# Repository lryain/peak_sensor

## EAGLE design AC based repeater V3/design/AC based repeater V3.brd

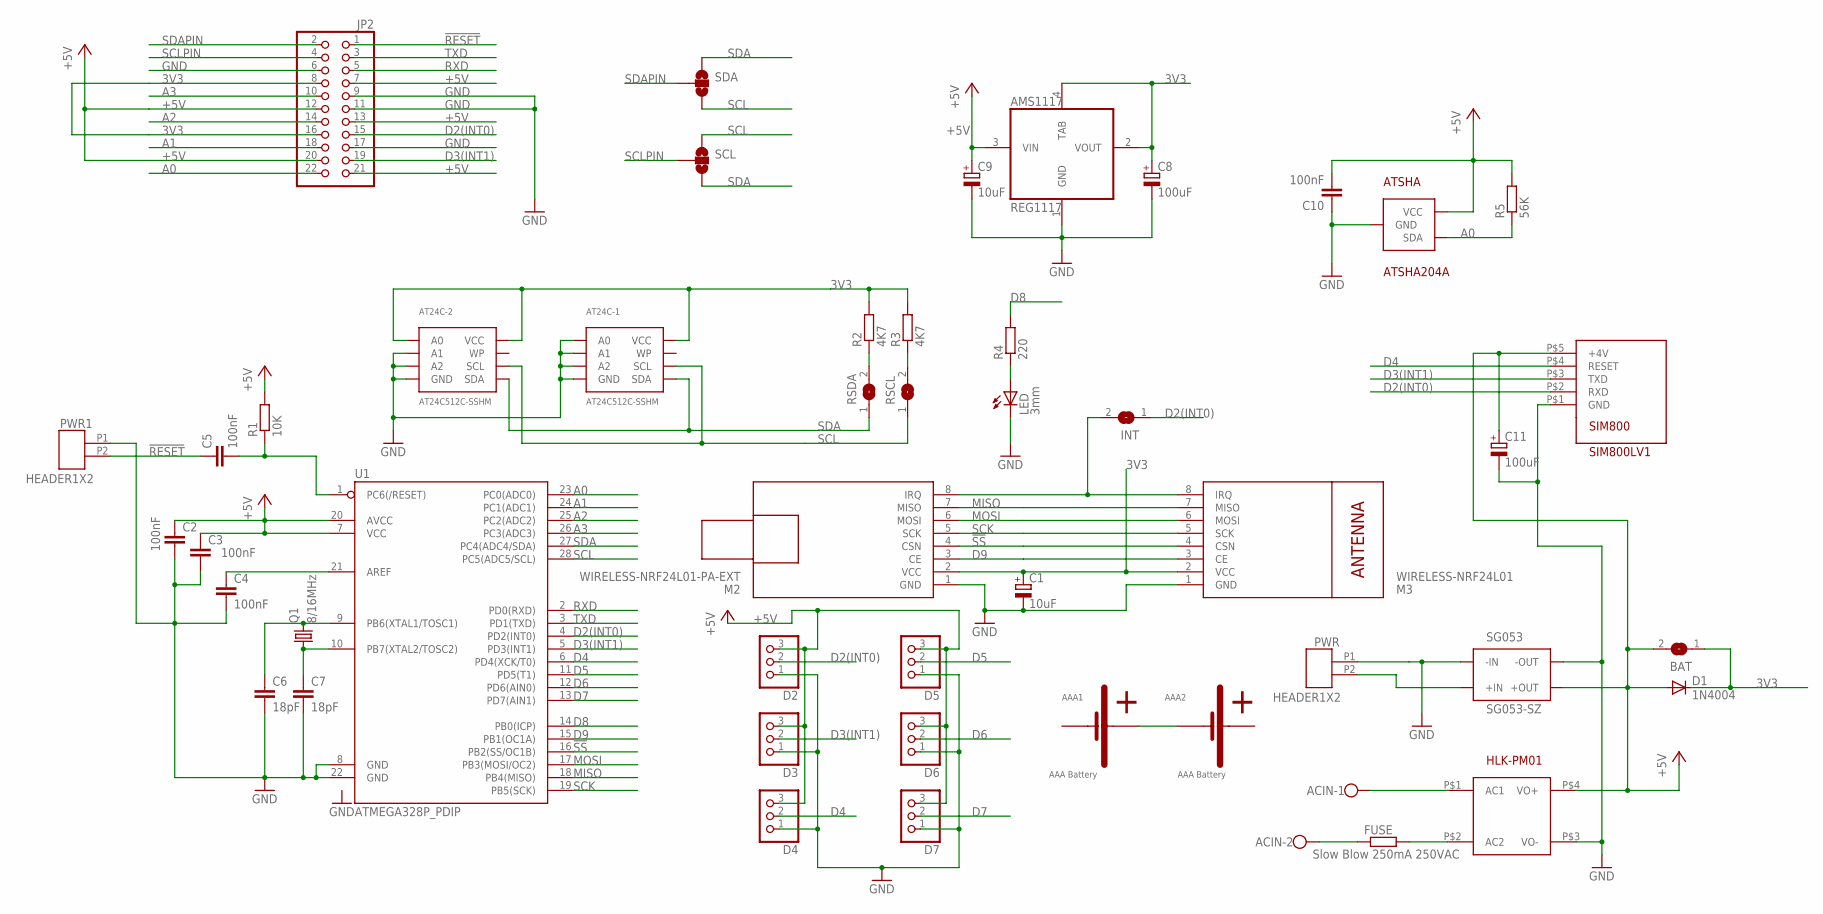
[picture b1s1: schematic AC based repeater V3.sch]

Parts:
AAA1: AAA Battery; AAABATTERYHOLDERPLUSPIN
AAA2: AAA Battery; AAABATTERYHOLDERMINPIN
ACIN: W237-102
AMS1117: REG1117; SOT223
AT24C-1, AT24C-2: AT24C512C-SSHM; SOIC8
ATSHA: ATSHA204A; SOT23-R
BAT: SJ
C1, C9: 10uF; E2,5-5
C2, C3, C4, C5, C10: 100nF; C025-025X050
C6, C7: 18pF; C025-025X050
C8, C11: 100uF; E3,5-8
D1: 1N4004; DO41-10
D2, D3, D4, D5, D6, D7: PINHD-1X3PTH; 1X03
FUSE: Slow Blow 250mA 250VAC; 0411V
HLK-PM01: HLK-PM01
INT: SJ
JP2: PINHD-2X11; 2X11
LED: 3mm; LED3MM
M2: WIRELESS-NRF24L01-PA-EXT; WIRELESS-NRD24L01-PA-EXT
M3: WIRELESS-NRF24L01
PWR, PWR1: HEADER1X2
Q1: 8/16MHz; HC49U-V
R1: 10K; 0207/7
R2, R3: 4K7; 0207/7
R4: 220; 0207/7
R5: 56K; 0207/7
RSCL: SJ
RSDA: SJ
SCL: JUMPER-PAD-3-NC_BY_TRACE; PAD-JUMPER-3-3OF3_NC_BY_TRACE_YES_SILK_FULL_BOX
SDA: JUMPER-PAD-3-NC_BY_TRACE; PAD-JUMPER-3-3OF3_NC_BY_TRACE_YES_SILK_FULL_BOX
SG053: SG053-SZ
SIM800: SIM800LV1
U1: ATMEGA328P_PDIP; DIL28-3

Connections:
3V3: AMS1117.2 (VOUT), AMS1117.4 (TAB), AT24C-1.8 (VCC), AT24C-2.1 (A0), AT24C-2.8 (VCC), BAT.1, C1.+, C8.+, D1.C, JP2.8, JP2.16, M2.2 (VCC), M3.2 (VCC), R2.2, R3.2
!RESET: C5.1, JP2.1, PWR1.P2
!SS: M2.4 (CSN), M3.4 (CSN), U1.16 (PB2(SS/OC1B))
+5V: AMS1117.3 (VIN), ATSHA.2 (VCC), BAT.2, C2.1, C3.1, C9.+, C10.2, C11.+, D1.A, D2.3, D3.3, D4.3, D5.3, D6.3, D7.3, HLK-PM01.P$4 (VO+), JP2.7, JP2.12, JP2.13, JP2.20, JP2.21, R1.2, R5.2, SG053.P$5 (+OUT), SG053.P$6 (+OUT), SIM800.P$5 (+4V), U1.7 (VCC), U1.20 (AVCC)
A0: ATSHA.1 (SDA), JP2.22, R5.1, U1.23 (PC0(ADC0))
A1: JP2.18, U1.24 (PC1(ADC1))
A2: JP2.14, U1.25 (PC2(ADC2))
A3: JP2.10, U1.26 (PC3(ADC3))
D2(INT0): D2.2, INT.1, JP2.15, SIM800.P$2 (RXD), U1.4 (PD2(INT0))
D3(INT1): D3.2, JP2.19, SIM800.P$3 (TXD), U1.5 (PD3(INT1))
D4: D4.2, SIM800.P$4 (RESET), U1.6 (PD4(XCK/T0))
D5: D5.2, U1.11 (PD5(T1))
D6: D6.2, U1.12 (PD6(AIN0))
D7: D7.2, U1.13 (PD7(AIN1))
D8: R4.2, U1.14 (PB0(ICP))
D9: M2.3 (CE), M3.3 (CE), U1.15 (PB1(OC1A))
GND: AMS1117.1 (GND), AT24C-1.1 (A0), AT24C-1.2 (A1), AT24C-1.3 (A2), AT24C-1.4 (GND), AT24C-2.2 (A1), AT24C-2.3 (A2), AT24C-2.4 (GND), ATSHA.3 (GND), C1.-, C2.2, C3.2, C4.2, C6.2, C7.2, C8.-, C9.-, C10.1, C11.-, D2.1, D3.1, D4.1, D5.1, D6.1, D7.1, HLK-PM01.P$3 (VO-), JP2.6, JP2.9, JP2.11, JP2.17, LED.K (C), M2.1 (GND), M3.1 (GND), PWR.P1, PWR1.P1, SG053.P$1 (-IN), SG053.P$2 (-IN), SG053.P$7 (-OUT), SG053.P$8 (-OUT), SIM800.P$1 (GND), U1.8 (GND), U1.22 (GND)
MISO: M2.7 (MISO), M3.7 (MISO), U1.18 (PB4(MISO))
MOSI: M2.6 (MOSI), M3.6 (MOSI), U1.17 (PB3(MOSI/OC2))
unnamed: PWR.P2, SG053.P$3 (+IN), SG053.P$4 (+IN)
unnamed: R2.1, RSDA.2
unnamed: ACIN.2, FUSE.1
unnamed: C4.1, U1.21 (AREF)
unnamed: R3.1, RSCL.2
unnamed: AAA1.P$2, AAA2.P$1
unnamed: ACIN.1, HLK-PM01.P$1 (AC1)
unnamed: FUSE.2, HLK-PM01.P$2 (AC2)
unnamed: C5.2, R1.1, U1.1 (PC6(/RESET))
unnamed: INT.2, M2.8 (IRQ), M3.8 (IRQ)
unnamed: LED.A, R4.1
unnamed: C6.1, Q1.2, U1.9 (PB6(XTAL1/TOSC1))
unnamed: C7.1, Q1.1, U1.10 (PB7(XTAL2/TOSC2))
RXD: JP2.5, U1.2 (PD0(RXD))
SCK: M2.5 (SCK), M3.5 (SCK), U1.19 (PB5(SCK))
SCL: AT24C-1.6 (SCL), AT24C-2.6 (SCL), RSCL.1, SCL.1, SDA.3, U1.28 (PC5(ADC5/SCL))
SCLPIN: JP2.4, SCL.2
SDA: AT24C-1.5 (SDA), AT24C-2.5 (SDA), RSDA.1, SCL.3, SDA.1, U1.27 (PC4(ADC4/SDA))
SDAPIN: JP2.2, SDA.2
TXD: JP2.3, U1.3 (PD1(TXD))

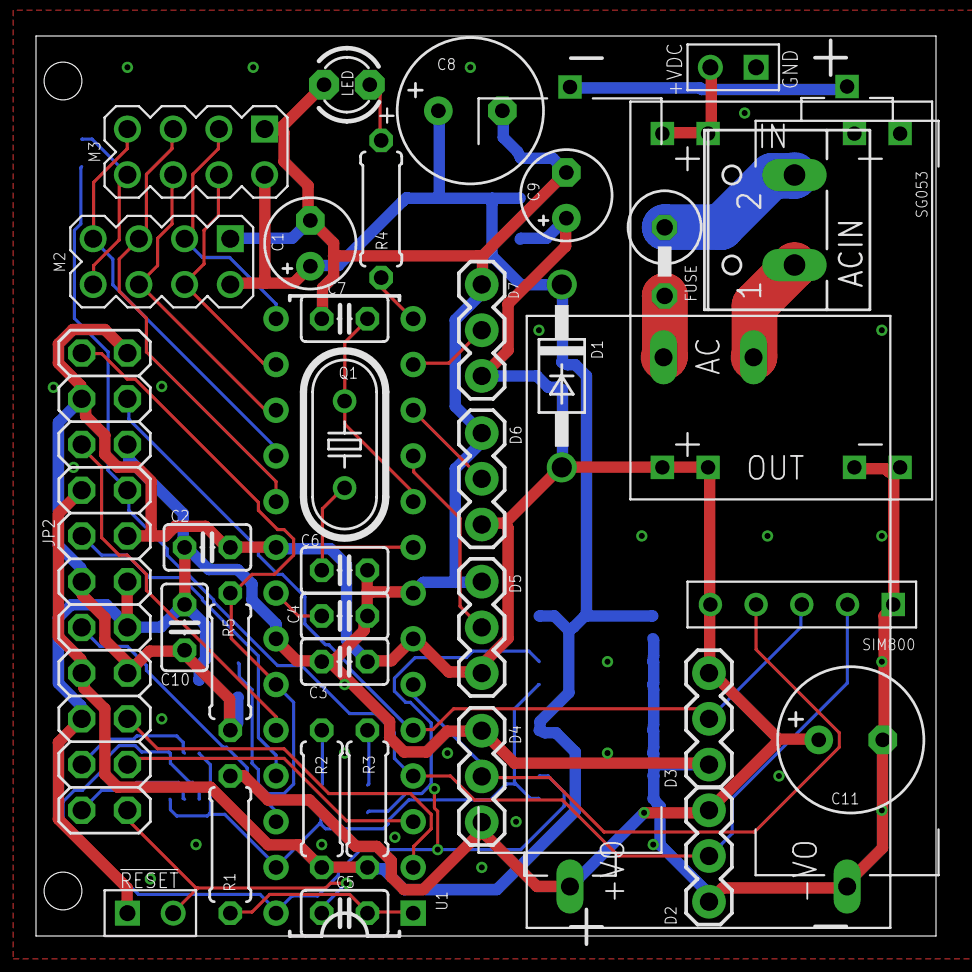
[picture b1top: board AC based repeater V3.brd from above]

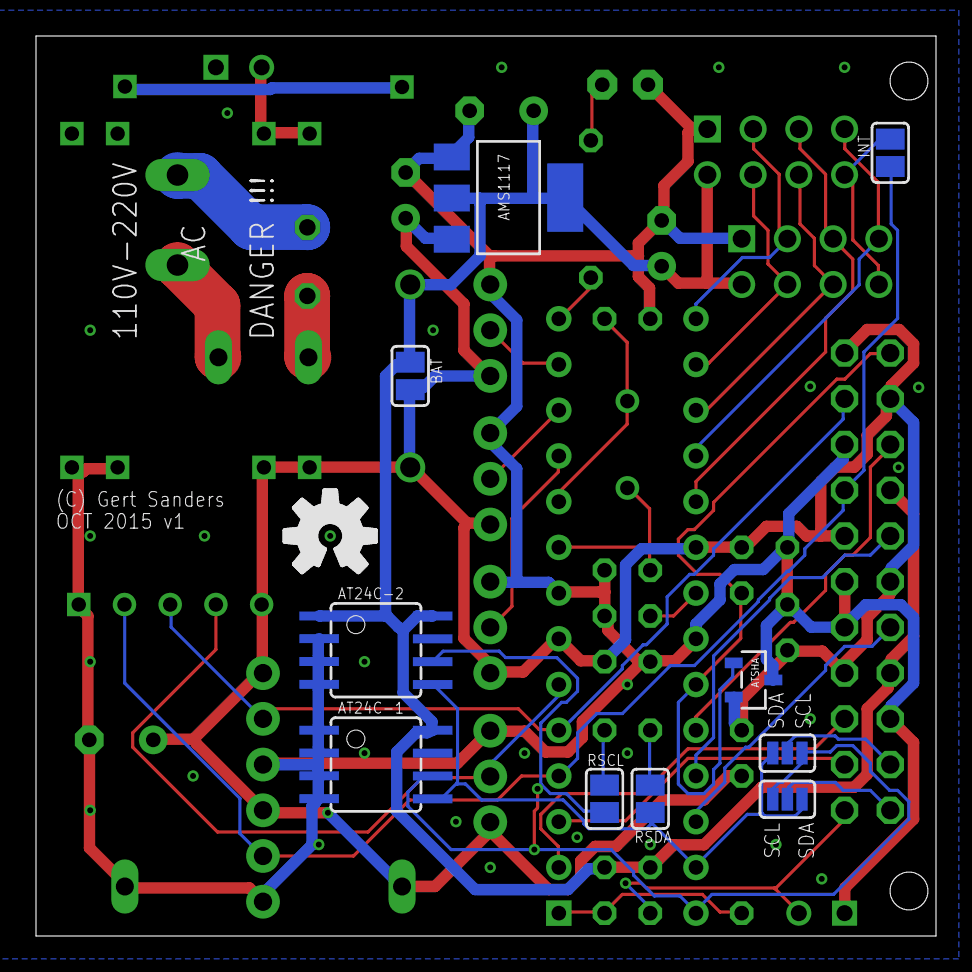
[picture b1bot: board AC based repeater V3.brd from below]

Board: 2 copper layers, 50.0 x 50.0 mm, 49 parts (11 on the bottom side), 39 nets.

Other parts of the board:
U$1: OSHWLOGO_TOL_0.2

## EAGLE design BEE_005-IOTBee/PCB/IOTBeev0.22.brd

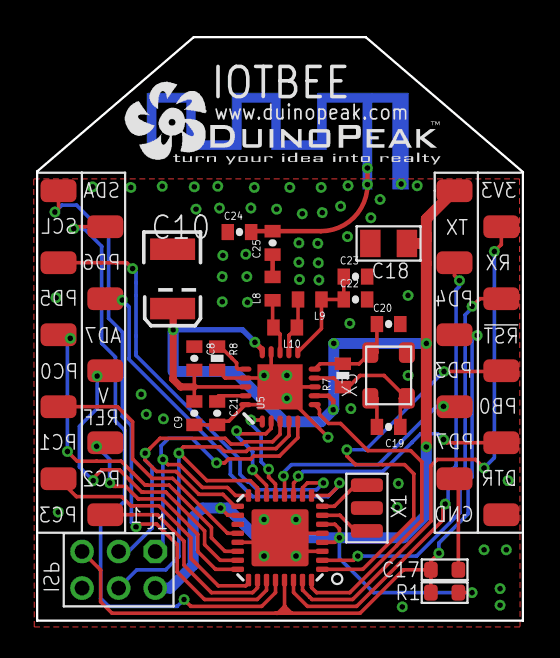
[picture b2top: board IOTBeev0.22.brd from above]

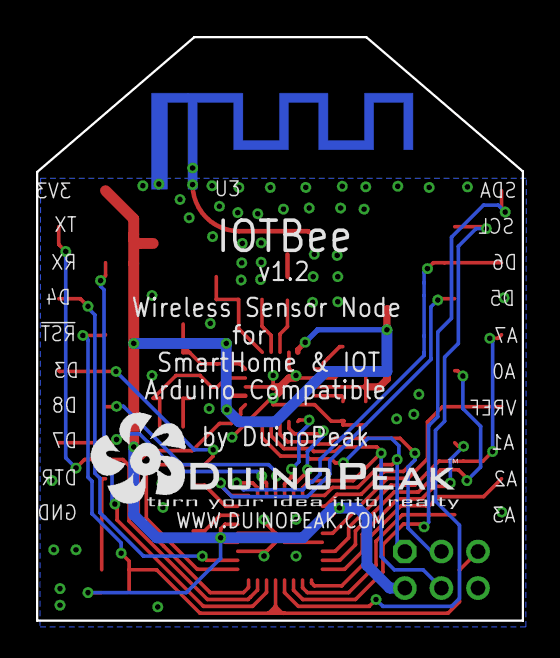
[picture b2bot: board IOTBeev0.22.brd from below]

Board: 2 copper layers, 27.0 x 32.4 mm, 27 parts (3 on the bottom side), 37 nets.

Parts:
ANT1: 2.4G-ANT
C8: 10nF; 0402-CAP
C9: 1nF; 0402-CAP
C10: 10uF; EIA3528
C17: 100nF; 0603_S
C18: 10u; 0805
C19, C20: 22pF; 0402-CAP
C21: 33nF; 0402-CAP
C22: 2.2nF; 0402-CAP
C23: 4.7pF; 0402-CAP
C24: 1.0pF; 0402-CAP
C25: 1.5pF; 0402-CAP
J1: CK_2X3_2.0
L8: 3.9nH; C0402
L9: 2.7nH; C0402
L10: 8.2nH; C0402
R1: 10k; 0603_S
R7: 1M; 0402-RES
R8: 22K; 0402-RES
U1: MEGA8; MLF32X
U3: 20P-SMD-2.0-BT
U5: NRF24L01ALT1; QFN20_ALT1
U$2: DUINOPEAK-LOGO-0.6
U$3: DUINOPEAK-LOGO-0.7
X1: 8MHz; XTAL_3X2
X3: 16MHz; X3225

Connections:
!RESET: C17.2, J1.3, R1.2, U1.29, U3.5
+3V3: C8.2, C9.2, C10.A, C18.1, J1.6, R1.1, U1.4, U1.6, U1.18, U3.1, U5.7, U5.15, U5.18
ADC7: U1.22, U3.16
ANT: ANT1.2, C24.2, C25.2
AREF: U1.20, U3.14
CE: U1.13, U5.1
CSN: U1.14, U5.2
DTR: C17.1, U3.9
GND: ANT1.1, C8.1, C9.1, C10.C, C18.2, C19.2, C20.2, C21.2, C22.2, C23.2, C24.1, J1.4, R8.2, U1.3, U1.5, U1.21, U1.HEAT, U3.10, U5.0, U5.8, U5.14, U5.17, U5.20, X1.2, X3.1, X3.3
IRQ: U1.32, U5.6
MISO: J1.1, U1.16, U5.5
MOSI: J1.5, U1.15, U5.4
unnamed: U1.7, X1.1
unnamed: U1.8, X1.3
unnamed: C19.1, R7.1, U5.9, X3.2
unnamed: C20.1, R7.2, U5.10, X3.4
unnamed: L8.1, L10.2, U5.13
unnamed: C22.1, C23.1, L9.1, U5.11
unnamed: R8.1, U5.16
unnamed: C21.1, U5.19
unnamed: L9.2, L10.1, U5.12
unnamed: C25.1, L8.2
PB0: U1.12, U3.7
PC0: U1.23, U3.15
PC1: U1.24, U3.13
PC2: U1.25, U3.12
PC3: U1.26, U3.11
PD3: U1.1, U3.6
PD4: U1.2, U3.4
PD5: U1.9, U3.17
PD6: U1.10, U3.18
PD7: U1.11, U3.8
RX: U1.30, U3.3
SCK: J1.2, U1.17, U5.3
SCL: U1.28, U3.19
SDA: U1.27, U3.20
TX: U1.31, U3.2

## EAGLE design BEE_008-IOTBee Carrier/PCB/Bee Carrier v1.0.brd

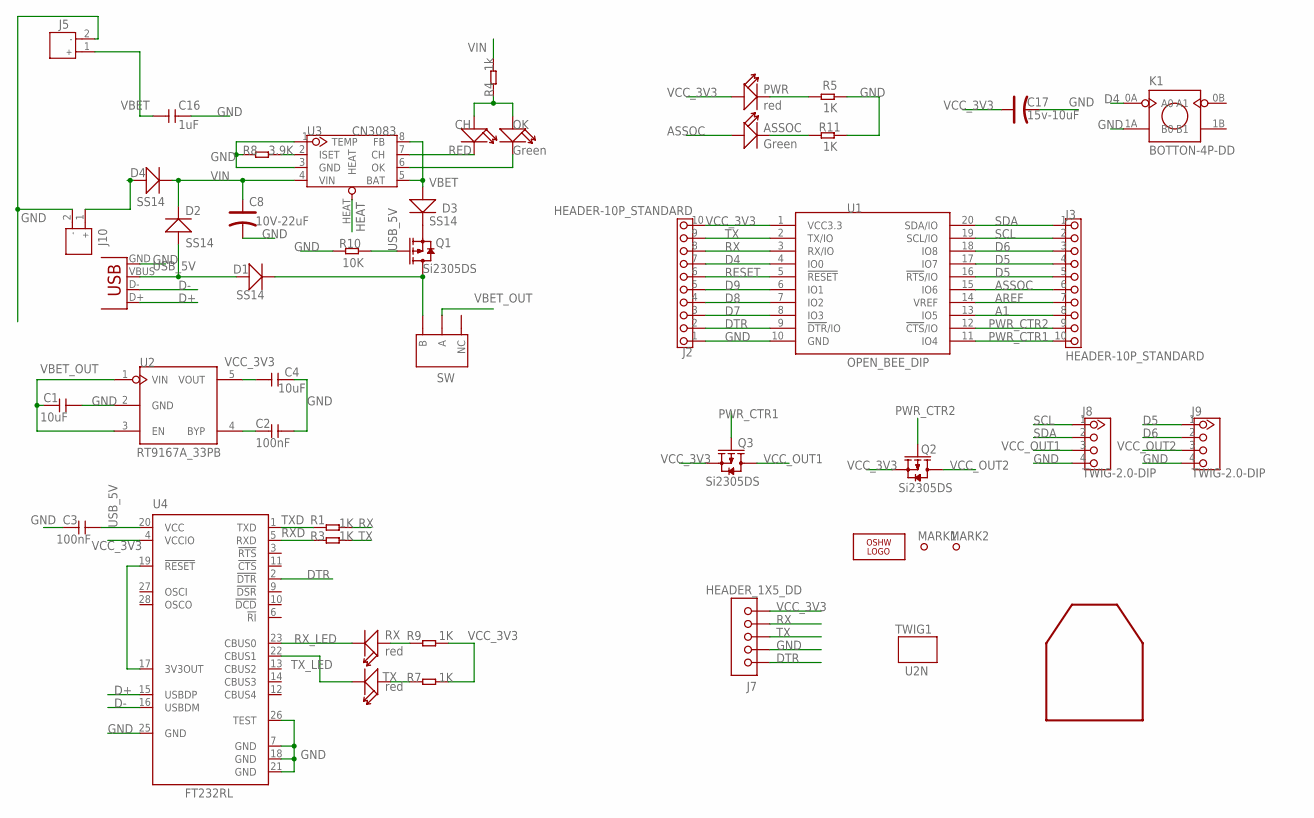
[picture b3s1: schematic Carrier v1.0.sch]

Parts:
ASSOC: Green; D0603
C1, C4: 10uF; 0805
C2, C3: 100nF; 0603
C8: 10V-22uF; AVX-B
C16: 1uF; 0805
C17: 15v-10uF; AVX-A
CH: RED; D0603
D1, D2, D3, D4: SS14; D2010
J2, J3: HEADER-10P_STANDARD; 2.54_10P
J5, J10: JST-2P-POWER-LEADED; 2P-2.0-LEADED-4.7X6.0
J7: HEADER_1X5_DD; CK_1X5
J8, J9: TWIG-2.0-DIP; 2.0_1X4
K1: BOTTON-4P-DD; BTN-S
LOGO2: OSHW_LOGO_FILLX0200-NT; OSHW_FILLX200_NOTEXT
MARK1, MARK2: PAD-MARK; MARK
OK: Green; D0603
PWR: red; D0805
Q1, Q2, Q3: Si2305DS; SOT23
R1, R3, R5, R7, R9, R11: 1K; 0603
R4: 1k; 0603
R8: 3.9K; 0603
R10: 10K; 0603
RX: red; D0603
SW: SWITCH-3P; 008-SW-3P-DIP
TWIG1: U2N; U2N_SILK
TX: red; D0603
U1: OPEN_BEE_DIP; CCBEE-PRO
U2: RT9167A_33PB; SOT23-5
U3: CN3083; SOP8
U4: FT232RL; SSOP28
U$1: WIFI_SILK
X1: USB-SMD-NS; USB-MINIB-NOSTOP

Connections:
A1: J3.8, U1.13 (IO5); also elsewhere on the board
AREF: J3.7, U1.14 (VREF); also elsewhere on the board
ASSOC: ASSOC.+, J3.6, U1.15 (IO6); also elsewhere on the board
D4: J2.7, K1.0A (A0), U1.4 (IO0); also elsewhere on the board
D5: J3.4, J3.5, J9.1, U1.16 (!RTS!/IO), U1.17 (IO7); also elsewhere on the board
D6: J3.3, J9.2, U1.18 (IO8); also elsewhere on the board
D7: J2.3, U1.8 (IO3); also elsewhere on the board
D8: J2.4, U1.7 (IO2); also elsewhere on the board
D9: J2.5, U1.6 (IO1); also elsewhere on the board
D+: U4.15 (USBDP), X1.D+
D-: U4.16 (USBDM), X1.D-
DTR: J2.2, J7.1, U1.9 (!DTR!/IO), U4.2 (!DTR); also elsewhere on the board
GND: C1.2, C2.2, C3.1, C4.2, C8.-, C16.2, C17.-, J2.1, J5.2, J7.2, J8.4, J9.4, J10.2, K1.1A (B0), R5.1, R8.1, R10.1, R11.1, U1.10 (GND), U2.2 (GND), U3.1 (TEMP), U3.3 (GND), U4.7 (GND), U4.18 (GND), U4.21 (GND), U4.25 (GND), U4.26 (TEST), X1.GND; also elsewhere on the board
HEAT: U3.HEAT
unnamed: PWR.-, R5.2
unnamed: R8.2, U3.2 (ISET)
unnamed: D4.+, J10.1
unnamed: C2.1, U2.4 (BYP)
unnamed: CH.-, U3.7 (CH)
unnamed: OK.-, U3.6 (OK)
unnamed: CH.+, OK.+, R4.1
unnamed: U4.17 (3V3OUT), U4.19 (!RESET)
unnamed: D3.-, Q1.2 (S)
unnamed: ASSOC.-, R11.2
unnamed: D1.-, Q1.3 (D), SW.P$3 (B)
unnamed: R9.1, RX.+
unnamed: R7.1, TX.+
PWR_CTR1: J3.10, Q3.1 (G), U1.11 (IO4); also elsewhere on the board
PWR_CTR2: J3.9, Q2.1 (G), U1.12 (!CTS!/IO); also elsewhere on the board
RESET: J2.6, U1.5 (!RESET); also elsewhere on the board
RX: J2.8, J7.4, R1.2, U1.3 (RX/IO); also elsewhere on the board
RXD: R3.1, U4.5 (RXD)
RX_LED: RX.-, U4.23 (CBUS0)
SCL: J3.2, J8.1, U1.19 (SCL/IO); also elsewhere on the board
SDA: J3.1, J8.2, U1.20 (SDA/IO); also elsewhere on the board
TX: J2.9, J7.3, R3.2, U1.2 (TX/IO); also elsewhere on the board
TXD: R1.1, U4.1 (TXD)
TX_LED: TX.-, U4.22 (CBUS1)
USB_5V: C3.2, D1.+, D2.+, Q1.1 (G), R10.2, U4.20 (VCC), X1.VBUS
VBET: C16.1, D3.+, J5.1, U3.5 (BAT), U3.8 (FB)
VBET_OUT: C1.1, SW.P$2 (A), U2.1 (VIN), U2.3 (EN)
VCC_3V3: C4.1, C17.+, J2.10, J7.5, PWR.+, Q2.2 (S), Q3.2 (S), R7.2, R9.2, U1.1 (VCC3.3), U2.5 (VOUT), U4.4 (VCCIO); also elsewhere on the board
VCC_OUT1: J8.3, Q3.3 (D)
VCC_OUT2: J9.3, Q2.3 (D)
VIN: C8.+, D2.-, D4.-, R4.2, U3.4 (VIN)

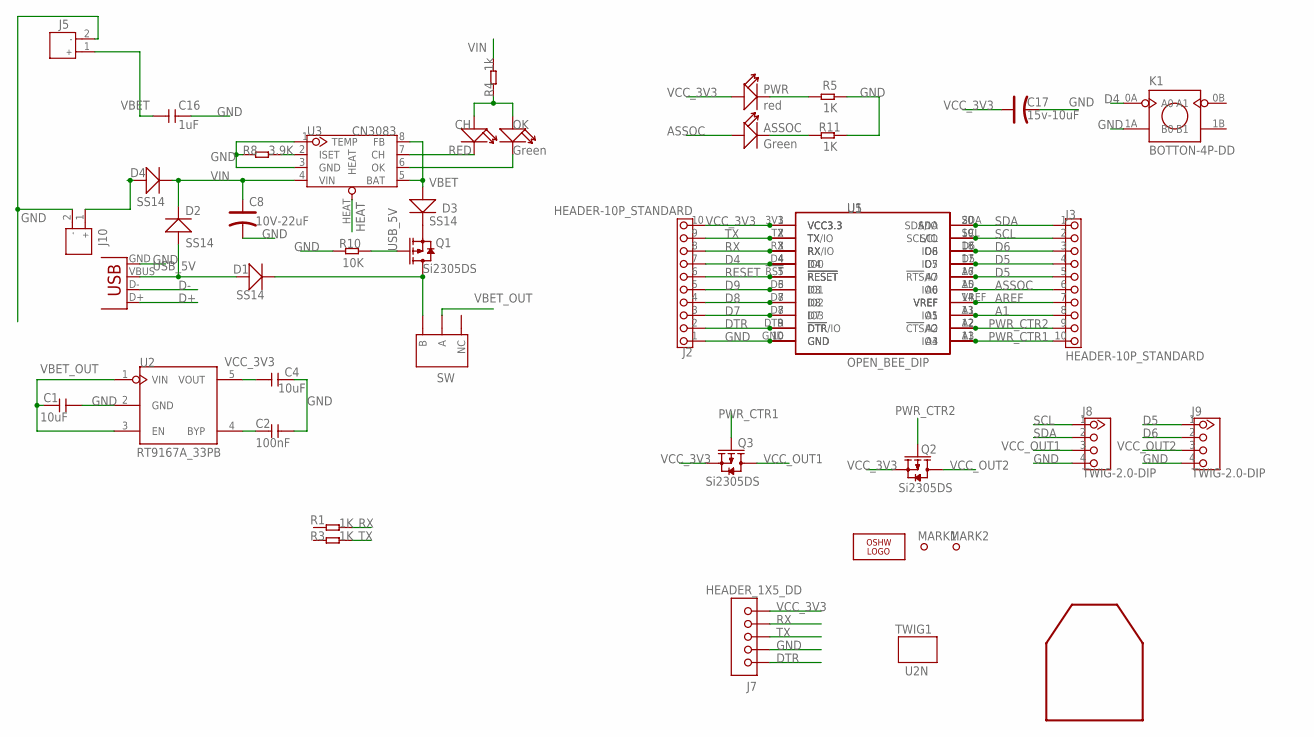
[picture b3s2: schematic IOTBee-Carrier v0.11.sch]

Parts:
ASSOC: Green; D0603
C1, C4: 10uF; 0805
C2: 100nF; 0603
C8: 10V-22uF; AVX-B
C16: 1uF; 0805
C17: 15v-10uF; AVX-A
CH: RED; D0603
D1, D2, D3, D4: SS14; D2010
J2, J3: HEADER-10P_STANDARD; 2.54_10P
J5, J10: JST-2P-POWER-LEADED; 2P-2.0-LEADED-4.7X6.0
J7: HEADER_1X5_DD; CK_1X5
J8, J9: TWIG-2.0-DIP; 2.0_1X4
K1: BOTTON-4P-DD; BTN-S
LOGO2: OSHW_LOGO_FILLX0200-NT; OSHW_FILLX200_NOTEXT
MARK1, MARK2: PAD-MARK; MARK
OK: Green; D0603
PWR: red; D0805
Q1, Q2, Q3: Si2305DS; SOT23
R1, R3, R5, R11: 1K; 0603
R4: 1k; 0603
R8: 3.9K; 0603
R10: 10K; 0603
SW: SWITCH-3P; 008-SW-3P-DIP
TWIG1: U2N; U2N_SILK
U1: OPEN_BEE_DIP; CCBEE-PRO
U2: RT9167A_33PB; SOT23-5
U3: CN3083; SOP8
U5: BEE-IOTBEE-IOTBEE-SOCKET; IOT_BEE_SMD
U$1: WIFI_SILK
X1: USB-SMD-NS; USB-MINIB-NOSTOP

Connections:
A1: J3.8, U1.13 (IO5), U5.A1
AREF: J3.7, U1.14 (VREF), U5.VREF
ASSOC: ASSOC.+, J3.6, U1.15 (IO6), U5.A0
D4: J2.7, K1.0A (A0), U1.4 (IO0), U5.D4
D5: J3.4, J3.5, J9.1, U1.16 (!RTS!/IO), U1.17 (IO7), U5.A7, U5.D5
D6: J3.3, J9.2, U1.18 (IO8), U5.D6
D7: J2.3, U1.8 (IO3), U5.D7
D8: J2.4, U1.7 (IO2), U5.D8
D9: J2.5, U1.6 (IO1), U5.D3
D+: X1.D+; also elsewhere on the board
D-: X1.D-; also elsewhere on the board
DTR: J2.2, J7.1, U1.9 (!DTR!/IO), U5.DTR (!DTR); also elsewhere on the board
GND: C1.2, C2.2, C4.2, C8.-, C16.2, C17.-, J2.1, J5.2, J7.2, J8.4, J9.4, J10.2, K1.1A (B0), R5.1, R8.1, R10.1, R11.1, U1.10 (GND), U2.2 (GND), U3.1 (TEMP), U3.3 (GND), U5.GND, X1.GND; also elsewhere on the board
HEAT: U3.HEAT
unnamed: PWR.-, R5.2
unnamed: R8.2, U3.2 (ISET)
unnamed: D4.+, J10.1
unnamed: C2.1, U2.4 (BYP)
unnamed: CH.-, U3.7 (CH)
unnamed: OK.-, U3.6 (OK)
unnamed: CH.+, OK.+, R4.1
unnamed: D3.-, Q1.2 (S)
unnamed: ASSOC.-, R11.2
unnamed: D1.-, Q1.3 (D), SW.P$3 (B)
PWR_CTR1: J3.10, Q3.1 (G), U1.11 (IO4), U5.A3
PWR_CTR2: J3.9, Q2.1 (G), U1.12 (!CTS!/IO), U5.A2
RESET: J2.6, U1.5 (!RESET), U5.!RST (!RESET)
RX: J2.8, J7.4, R1.2, U1.3 (RX/IO), U5.RX
SCL: J3.2, J8.1, U1.19 (SCL/IO), U5.SCL
SDA: J3.1, J8.2, U1.20 (SDA/IO), U5.SDA
TX: J2.9, J7.3, R3.2, U1.2 (TX/IO), U5.TX
USB_5V: D1.+, D2.+, Q1.1 (G), R10.2, X1.VBUS; also elsewhere on the board
VBET: C16.1, D3.+, J5.1, U3.5 (BAT), U3.8 (FB)
VBET_OUT: C1.1, SW.P$2 (A), U2.1 (VIN), U2.3 (EN)
VCC_3V3: C4.1, C17.+, J2.10, J7.5, PWR.+, Q2.2 (S), Q3.2 (S), U1.1 (VCC3.3), U2.5 (VOUT), U5.3V3 (VCC3.3); also elsewhere on the board
VCC_OUT1: J8.3, Q3.3 (D)
VCC_OUT2: J9.3, Q2.3 (D)
VIN: C8.+, D2.-, D4.-, R4.2, U3.4 (VIN)

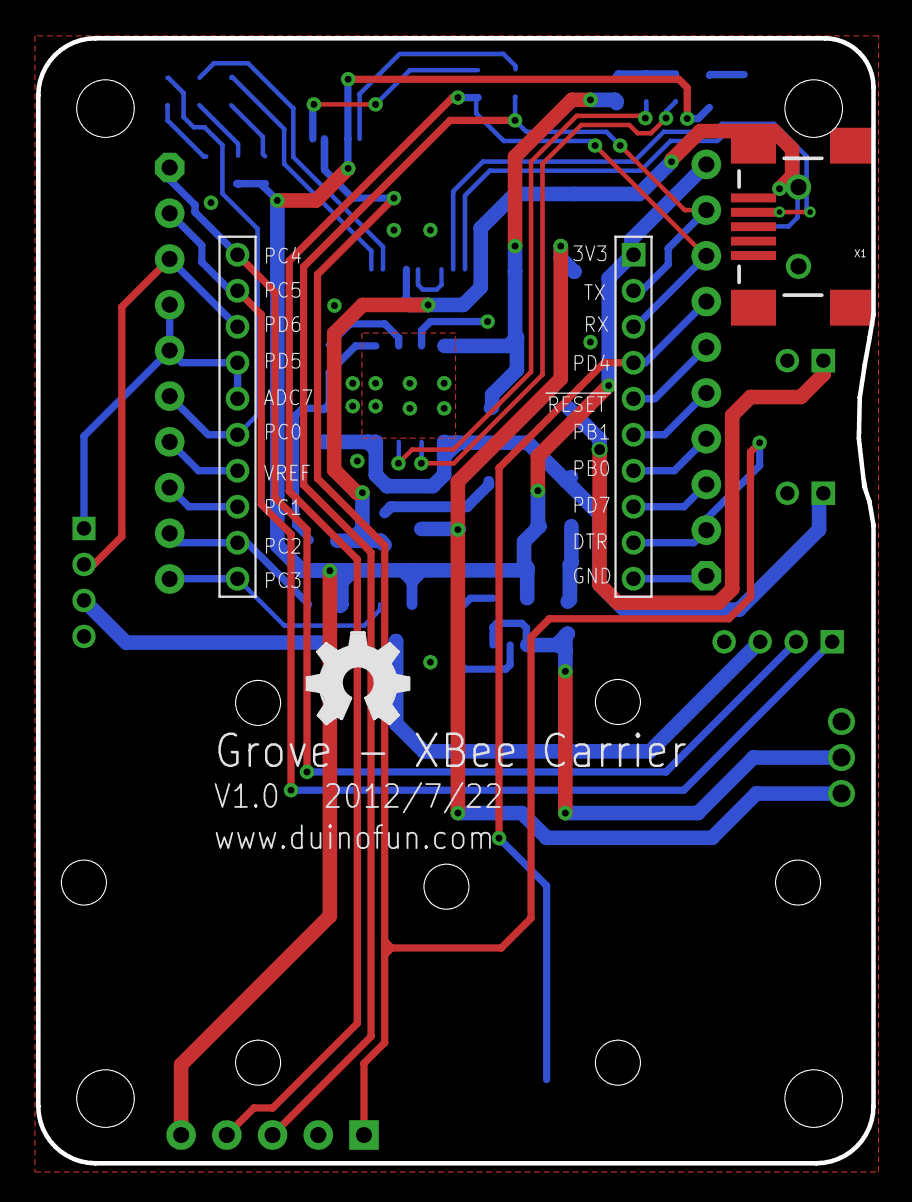
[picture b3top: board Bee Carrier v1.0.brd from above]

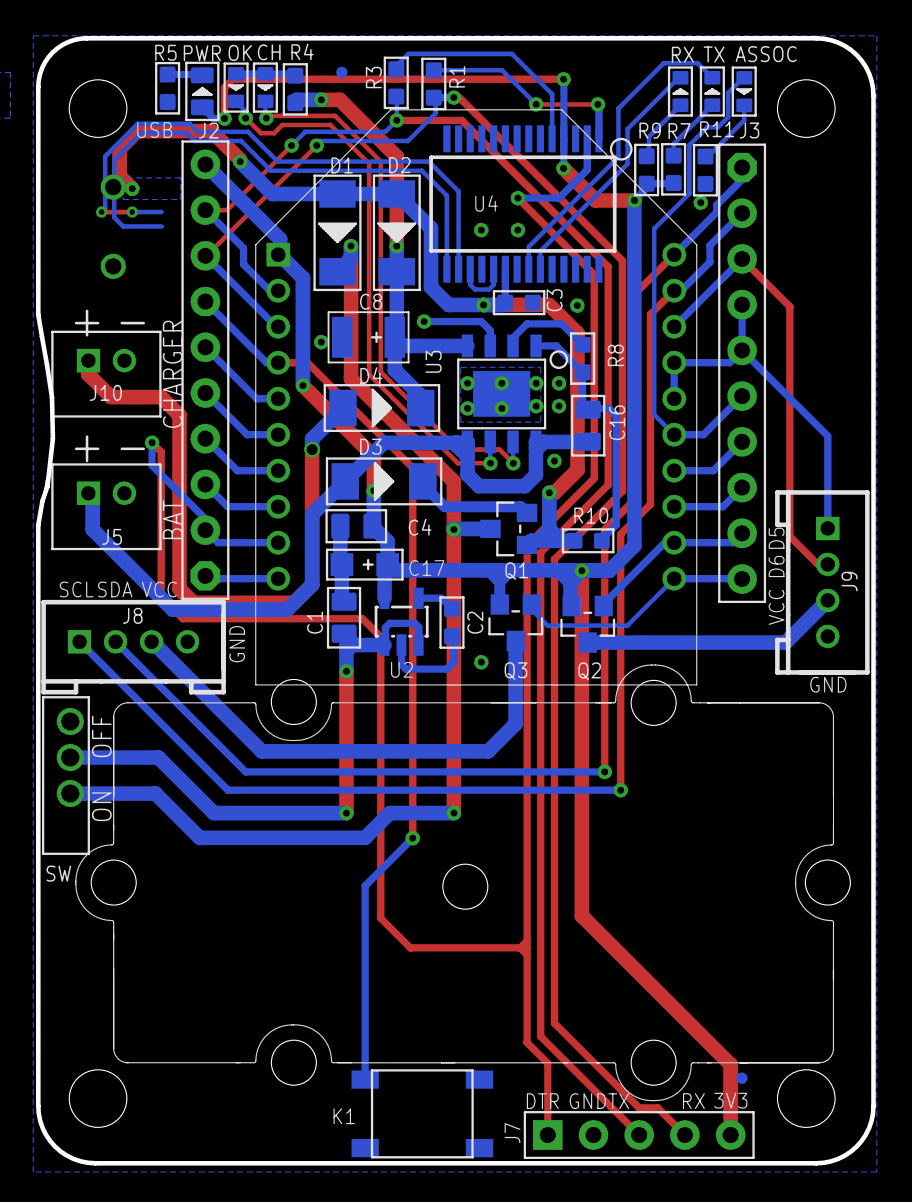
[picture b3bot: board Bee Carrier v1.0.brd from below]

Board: 2 copper layers, 46.5 x 62.5 mm, 48 parts (46 on the bottom side), 44 nets.

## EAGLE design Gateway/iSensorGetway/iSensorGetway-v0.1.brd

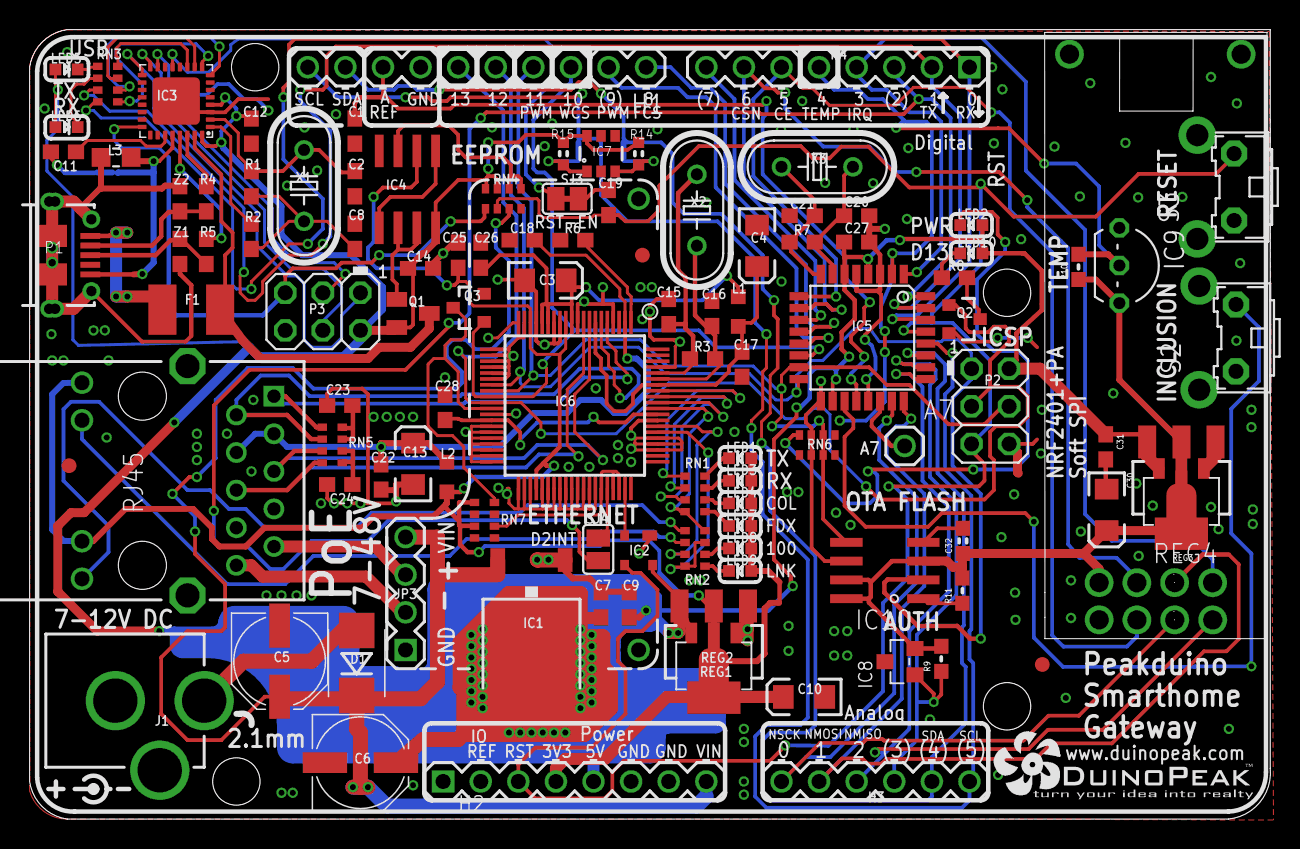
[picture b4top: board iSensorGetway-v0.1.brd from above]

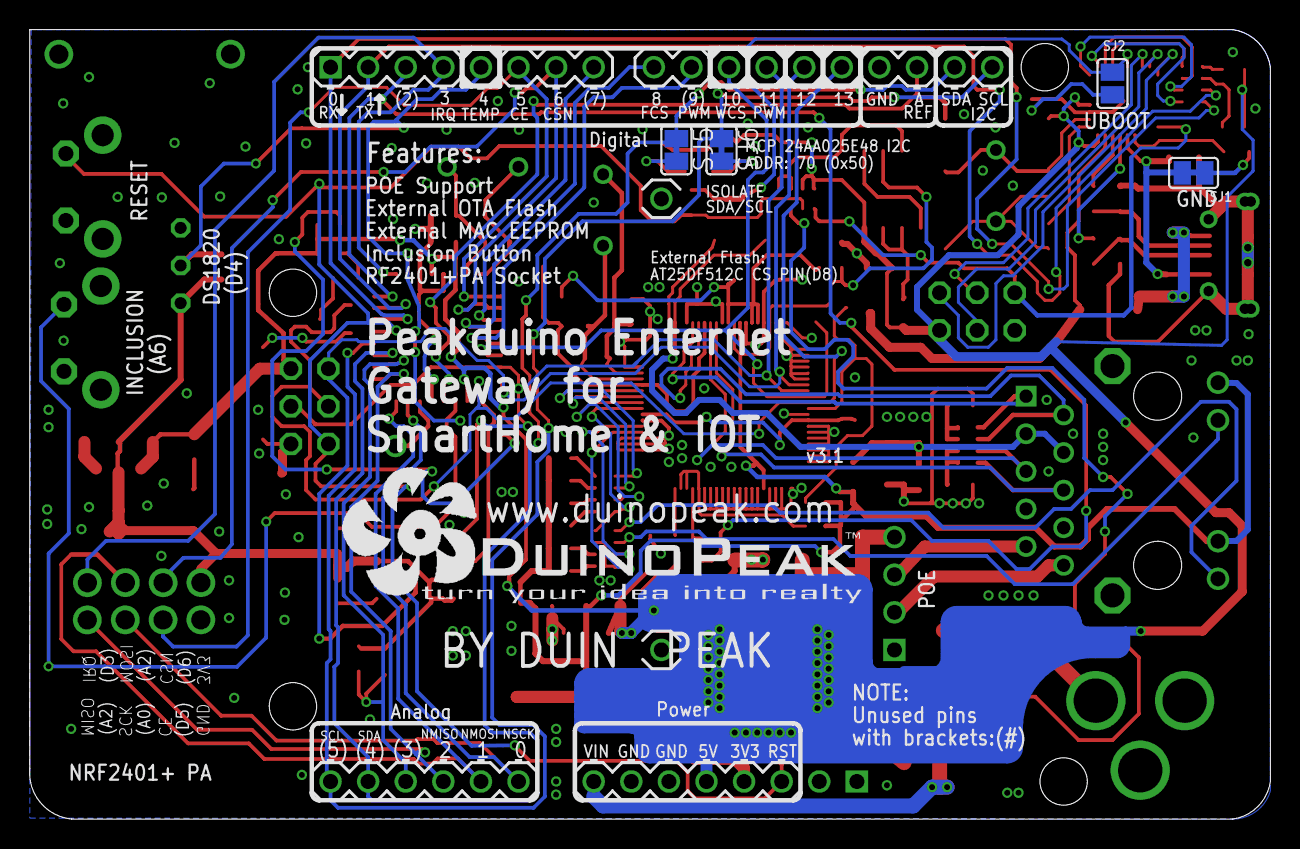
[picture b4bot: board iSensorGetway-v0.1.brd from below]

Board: 2 copper layers, 83.8 x 53.3 mm, 113 parts (5 on the bottom side), 98 nets.

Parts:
A7: M01PTH; 1X01
C1, C7, C12, C14, C19, C27: 100nF 0603; 0603
C2, C8, C20, C21: 22pF 0603; 0603
C3, C4, C10, C13, C30: 10uF 6.3V A TANT; EIA3216
C5, C6: 47uF 25V; PANASONIC_D
C9, C11, C31: 1uF 0603; 0603
C15, C16: 13pF; 0603
C17, C22, C23, C24, C25, C26, C28: 100nF; 0603
C18: 10nF; 0603
C32: 0.1u; 0603-CAP
D1: 1N4004 SMB; SMB-DIODE
F1: 500mA PTC 1812; L1812
FID1, FID2, FID3: FIDUCIAL1X2.5; FIDUCIAL-1X2.5
H1: Digital_8_13; 1X10
H2: Power; 1X08
H3: Analog; 1X06
H4: Digital_0_7; 1X08
IC1: MC33269DT-5.0; DPACK
IC2: APX811-44UG-7; SOT143-R
IC3: ATMEGA16U2-MU; ATMEL_QFN32
IC4: LM358D; SO08
IC5: ATMEGA328P TQFP32; TQFP32-08
IC6: W5100SQFP80; SQFP80
IC7: 24AA025E48; SOT23-6
IC8: ATSHA204A; SOT23
IC9: DS1820; TO92-
IC10: AT25DF512C-SSHN-B; SO-08
J1: DC_2_1MM; POWER_JACK_PTH
JP3: FT-POE-MODULE3; FT-POE-MODULE-NOLABEL
L1, L2: 1uH 250mA 0805; L2012C
L3: 0805 INDUCTOR; 0805-LARGE
LED1, LED3, LED9: YELLOW; LED-0603
LED2: PWR/BLUE; LED-0603
LED4: RED; LED-0603
LED5: TX/YEL; LED-0603
LED6: RX/GRN; LED-0603
LED7, LED8: GREEN; LED-0603
LED10: D13/RED; LED-0603
P1: USB-6PSMT; USB-MICROB-MB05PMXX
P2: ICSP:MAIN; 2X03
P3: ICSP:USB; 2X03
Q1: FDN340P; SOT23
Q2, Q3: 2N7002; SOT23-3
R1, R7: 1M 0603; 0603
R2: 27R 0603; 0603
R3: 1M; 0603
R4, R5: 22R 0603; 0603
R6: 12K3 1%; 0603
R8: 1K 0603; 0603
R9: 56k; 0603-RES
R10: 10k; 0603-RES
R11: 0603-RES
R14, R15: 4K7; 0603
REG1, REG4: LD1117-SOT89; SOT89
REG2, REG3: LD1117-SOT223; SOT223
RN1, RN2, RN3, RN6, RN7: 1K; CAY16
RN4: 10K; CAY16
RN5: 49R9 1%; CAY16
S2, S3: B3F-31XX
SJ1: GROUND; SJ
SJ2: UBOOT; SJ
SJ3: RESET-EN; SJ
SJ4: D2_INT; SJ
SJ5, SJ6: SJC
U1: HY931147C-RJ45; HY931147C
U$8: DUINOPEAK-LOGO-1.2
U$17: NRF2401; NRF2401_PA_OUTLINE
U$20: DUINOPEAK-LOGO-0.6
X1, X3: 16MHz; HC49U-V
X2: 25MHz; HC49U-V
Z1, Z2: PGB1010603; 0603

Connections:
1V8A: C4.A, C17.1, IC6.7, IC6.74, L1.2
1V8OUT: C28.1, IC6.33, IC6.69
1V8_OUT: C3.A, C26.1, IC6.11, IC6.15, IC6.16, L1.1
3V3A: C13.A, C18.1, C22.1, IC6.2, L2.2, U1.P$3, U1.P$4
3V3D: C10.A, C25.1, H2.4, IC4.2, IC6.12, IC6.18, IC6.44, L2.1, LED1.A, LED3.A, LED4.A, LED7.A, LED8.A, LED9.A, REG1.2, REG1.4, REG2.2, REG2.4, RN7.5, RN7.7, U1.P$11, U1.P$13
3V3_NRF24: C30.A, C32.1, IC8.2, IC9.3, IC10.3, IC10.7, IC10.8, R9.2, R10.1, R11.2, REG3.2, REG3.4, REG4.2, REG4.4, U$17.3V3
5V: C6.+, C7.1, C9.1, C12.1, C14.1, C27.1, C31.1, H2.5, IC1.2, IC2.4, IC3.4, IC3.32, IC4.8, IC5.4, IC5.6, IC5.18, IC7.6, LED2.A, LED5.A, LED6.A, LED10.A, P2.2, P3.2, Q1.2, R14.1, R15.1, REG1.3, REG2.3, REG3.3, REG4.3, RN4.7, RN4.8
A0_SCK: H3.1, IC5.23, U$17.SCK
A1_MOSI: H3.2, IC5.24, U$17.MOSI
A2_MISO: H3.3, IC5.25, U$17.MISO
A3: H3.4, IC5.26, IC8.1, R9.1
A4_SDA: H1.9, H3.5, IC5.27, SJ5.1
A5_SCL: H1.10, H3.6, IC5.28, SJ6.1
A6_INCLUSION: IC5.19, S2.2
A7: A7.1, IC5.22
AREF: C1.1, H1.8, IC5.20
COLLED: IC6.71, RN1.3
D0_RX: H4.1, IC5.30, RN3.4
D1_TX: H4.2, IC5.31, RN3.3
D2: H4.3, IC5.32, SJ4.1
D3_IRQ: H4.4, IC5.1, U$17.IRQ
D4_DS1820: H4.5, IC5.2, IC9.2, R10.2
D5_CE: H4.6, IC5.9, U$17.CE
D6_CSN: H4.7, IC5.10, U$17.CSN
D7: H4.8, IC5.11
D8: H1.1, IC5.12
D8_FLASH_CSN: IC10.1, R11.1
D9: H1.2, IC5.13
D10_SS: H1.3, IC5.14, IC6.29, Q3.1
D11_MOSI: H1.4, IC5.15, IC6.28, IC10.5, P2.4
D12_MISO: H1.5, IC5.16, IC6.27, IC10.2, P2.1
D13_SCK: H1.6, IC5.17, IC6.30, IC10.6, P2.3, Q2.1
DTR: IC3.13, SJ2.2, SJ3.1
FDXLED: IC6.70, RN1.4, RN2.8
GND: C1.2, C2.1, C3.C, C4.C, C5.-, C6.-, C7.2, C8.1, C9.2, C10.C, C11.2, C12.2, C13.C, C14.2, C15.2, C16.2, C17.2, C18.2, C20.1, C21.1, C22.2, C23.2, C24.2, C25.2, C26.2, C27.2, C28.2, C30.C, C31.2, C32.2, H1.7, H2.6, H2.7, IC1.1, IC2.1, IC3.3, IC3.EXP, IC4.4, IC5.3, IC5.5, IC5.21, IC6.4, IC6.10, IC6.13, IC6.14, IC6.17, IC6.19, IC6.20, IC6.21, IC6.22, IC6.23, IC6.24, IC6.25, IC6.26, IC6.32, IC6.34, IC6.35, IC6.36, IC6.37, IC6.38, IC6.39, IC6.40, IC6.41, IC6.42, IC6.43, IC6.45, IC6.46, IC6.47, IC6.48, IC6.49, IC6.50, IC6.51, IC6.52, IC6.53, IC6.54, IC6.63, IC6.64, IC6.65, IC6.68, IC6.77, IC7.2, IC7.4, IC7.5, IC8.3, IC9.1, IC10.4, J1.GND, J1.GNDBREAK, JP3.1, P2.6, P3.6, Q2.2, Q3.2, R6.1, REG1.1, REG2.1, REG3.1, REG4.1, RN4.4, RN6.1, S2.1, S3.1, SJ1.2, SJ2.1, U1.GND1, U1.GND2, U$17.GND
INT: IC6.56, SJ4.2
LINKLED: IC6.66, RN2.4, RN2.7
MISO2: IC3.17, P3.1
MOSI2: IC3.16, P3.4
unnamed: C24.1, RN5.5, RN5.6
unnamed: C20.2, IC5.7, R7.2, X3.2
unnamed: C19.1, SJ3.2
unnamed: LED10.C, R8.2
unnamed: IC7.1, R15.2, SJ6.2
unnamed: Q2.3, R8.1
unnamed: C21.2, IC5.8, R7.1, X3.1
unnamed: IC3.1, R2.1
unnamed: L3.1, P1.FIX1, P1.FIX2, P1.PIN1, P1.PIN2, P1.TAB1, P1.TAB2, Z1.2, Z2.2
unnamed: LED6.C, RN3.2
unnamed: IC4.3, RN4.5, RN4.6
unnamed: LED5.C, RN3.1
unnamed: LED2.C, RN6.8
unnamed: P1.D+, R5.2, Z1.1
unnamed: P1.D-, R4.2, Z2.1
unnamed: IC4.6, IC4.7, Q1.1
unnamed: IC4.1, IC4.5
unnamed: LED8.C, RN2.6
unnamed: IC6.55, IC6.57, IC6.58, RN7.2
unnamed: LED9.C, RN2.5
unnamed: IC7.3, R14.2, SJ5.2
unnamed: D1.A, J1.PWR
unnamed: RN2.1, U1.P$14
unnamed: JP3.3, U1.P$9
unnamed: JP3.2, U1.P$10
unnamed: C2.2, IC3.2, R1.2, X1.2
unnamed: C8.2, R1.1, R2.2, X1.1
unnamed: F1.1, P1.VBUS
unnamed: C11.1, IC3.27
unnamed: C23.1, RN5.7, RN5.8
unnamed: IC6.1, R6.2
unnamed: LED7.C, RN1.5
unnamed: LED4.C, RN1.6
unnamed: LED3.C, RN1.7
unnamed: LED1.C, RN1.8
unnamed: RN2.2, U1.P$12
RD+: IC3.29, R5.1
RD-: IC3.30, R4.1
RESET: C19.2, H2.3, IC2.3, IC5.29, P2.5, RN4.2, S3.2
RESET2: IC3.24, P3.5, RN4.1
RXIN: IC6.6, RN5.2, U1.P$2
RXIP: IC6.5, RN5.1, U1.P$1
RXLED: IC3.10, RN3.7
SCK2: IC3.15, P3.3
SEN: IC6.31, Q3.3, RN7.4
SPDLED: IC6.67, RN2.3
TXLED: IC3.11, RN3.8
TXON: IC6.9, RN5.4, U1.P$6
TXOP: IC6.8, RN5.3, U1.P$5
USBGND: IC3.28, L3.2, P1.GND, SJ1.1
USBRXD: IC3.9, RN3.5
USBTXD: IC3.8, RN3.6
USBVCC: F1.2, IC3.31, Q1.3
VIN: C5.+, D1.C, H2.8, IC1.3, JP3.4, RN4.3
WIZRST: IC2.2, IC6.59
WRXLED: IC6.72, RN1.2
WTXLED: IC6.73, RN1.1
XTLN: C16.1, IC6.75, R3.2, X2.2
XTLP: C15.1, IC6.76, R3.1, X2.1

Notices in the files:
parts and their libraries:
SparkFun-Connectors: Licensing: CC v3.0 Share-Alike You are welcome to use this library for commercial purposes.
SparkFun-DiscreteSemi: Licensing: Creative Commons ShareAlike 4.0 International - https://creativecommons.org/licenses/by-sa/4.0
